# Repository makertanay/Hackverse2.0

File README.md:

# Rakshak

 application which will be a GPS tracker connected to an ambulance. In many situations we have seen that the ambulance doesn't reach some places on time as the place might be difficult to find, so by creating an application through which the ambulance and the person called for ambulance gets and idea of where the ambulance is and not only that application tells you where the ambulance is but until it arrives it also tells you what first aid can you give it to the patient at the moment so as to keep the person alive until he reaches the hospital.

### Unique Selling Points

* Point 1. it has a GPS locator, so the person called in for an ambulance can track where the ambulance is.
* Point 2. It tells you some First Aid that can be provided to the patients
* Point 3. This can work even in remote areas as it is inked with the google maps
* Point 4. This also shows how much time will it take to reach the patient

## Implementation: 
Enter the details, the details would be given to the nearest ambulance then the website will show the fastest direction for the ambulance to reach the victim in the mean time it will show the first aid that can be given to the patient.
## Technology Stack  

### Tech1

fusion360

### Tech2

aruduino 

### Tech3

WebDev

## Picture/Screenshot 1

## Picture/Screenshot 2

## Picture/Screenshot 3

## Challanges
Implementation was difficult due to constraint on hardware usage.

## Getting Started

https://makertanay.github.io/Hackverse2.0/

## Future Aspects

Implementation with Hardware

## Authors
* [**Tanay**]https://github.com/makertanay
* [**Kaustubh**]https://github.com/kaustubhmohta
* [**Gauri**]https://github.com/kodekandy

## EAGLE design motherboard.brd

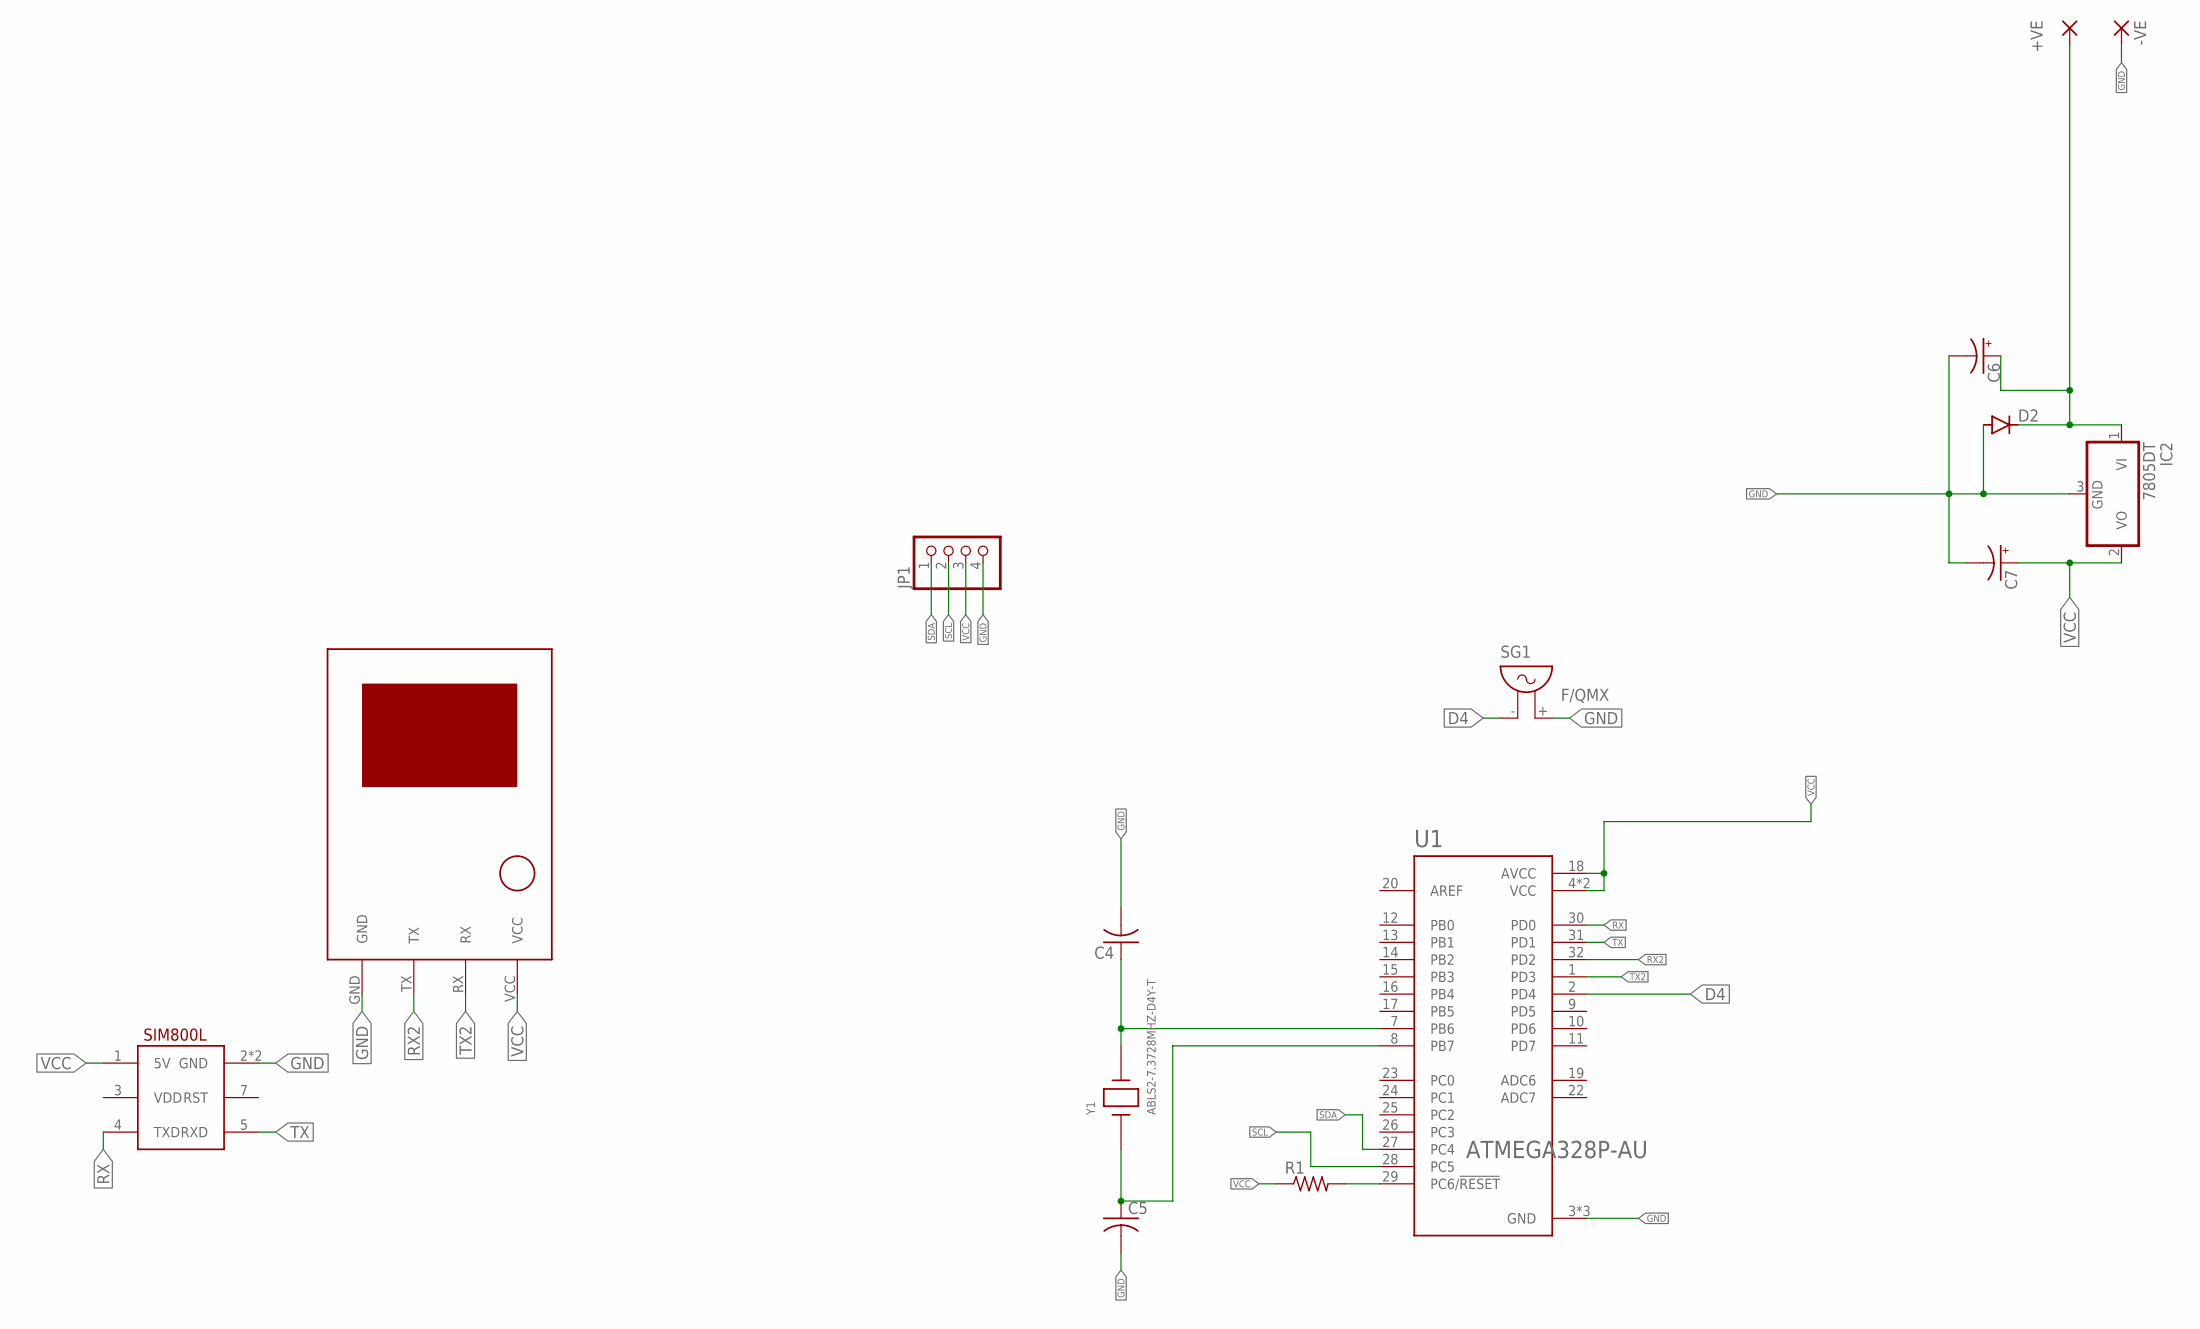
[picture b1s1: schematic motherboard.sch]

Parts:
+VE: WIREPAD1,6/0,8; 1,6/0,8
-VE: WIREPAD1,6/0,8; 1,6/0,8
C4, C5: C-US025-024X044; C025-024X044
C6, C7: CPOL-US153CLV-1010; 153CLV-1010
D2: DIODE-DO214AC; DO214AC
IC2: 7805DT; TO252
JP1: PINHD-1X4; 1X04
R1: R-US_R0603; R0603
SG1: F/QMX
U1: ATMEGA328P-AU; QFP80P900X900X120-32N
U$1: U-BLOX-NEO6V2
U$2: SIM800L; SIP
Y1: ABLS2-7.3728MHZ-D4Y-T; XTAL_ABLS2-7.3728MHZ-D4Y-T

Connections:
D4: SG1.- (1), U1.2 (PD4)
GND: -VE.1, C4.2, C5.2, C6.-, C7.-, D2.A, IC2.3 (GND), JP1.4, SG1.+ (2), U1.3 (GND), U1.5 (GND), U1.21 (GND), U$1.GND, U$2.2 (GND), U$2.6 (GND)
unnamed: +VE.1, C6.+, D2.C, IC2.1 (VI)
unnamed: C4.1, U1.7 (PB6), Y1.2
unnamed: C5.1, U1.8 (PB7), Y1.1
unnamed: R1.2, U1.29 (PC6/!RESET)
RX: U1.30 (PD0), U$2.4 (TXD)
RX2: U1.32 (PD2), U$1.TX
SCL: JP1.2, U1.28 (PC5)
SDA: JP1.1, U1.27 (PC4)
TX: U1.31 (PD1), U$2.5 (RXD)
TX2: U1.1 (PD3), U$1.RX
VCC: C7.+, IC2.2 (VO), JP1.3, R1.1, U1.4 (VCC), U1.6 (VCC), U1.18 (AVCC), U$1.VCC, U$2.1 (5V)

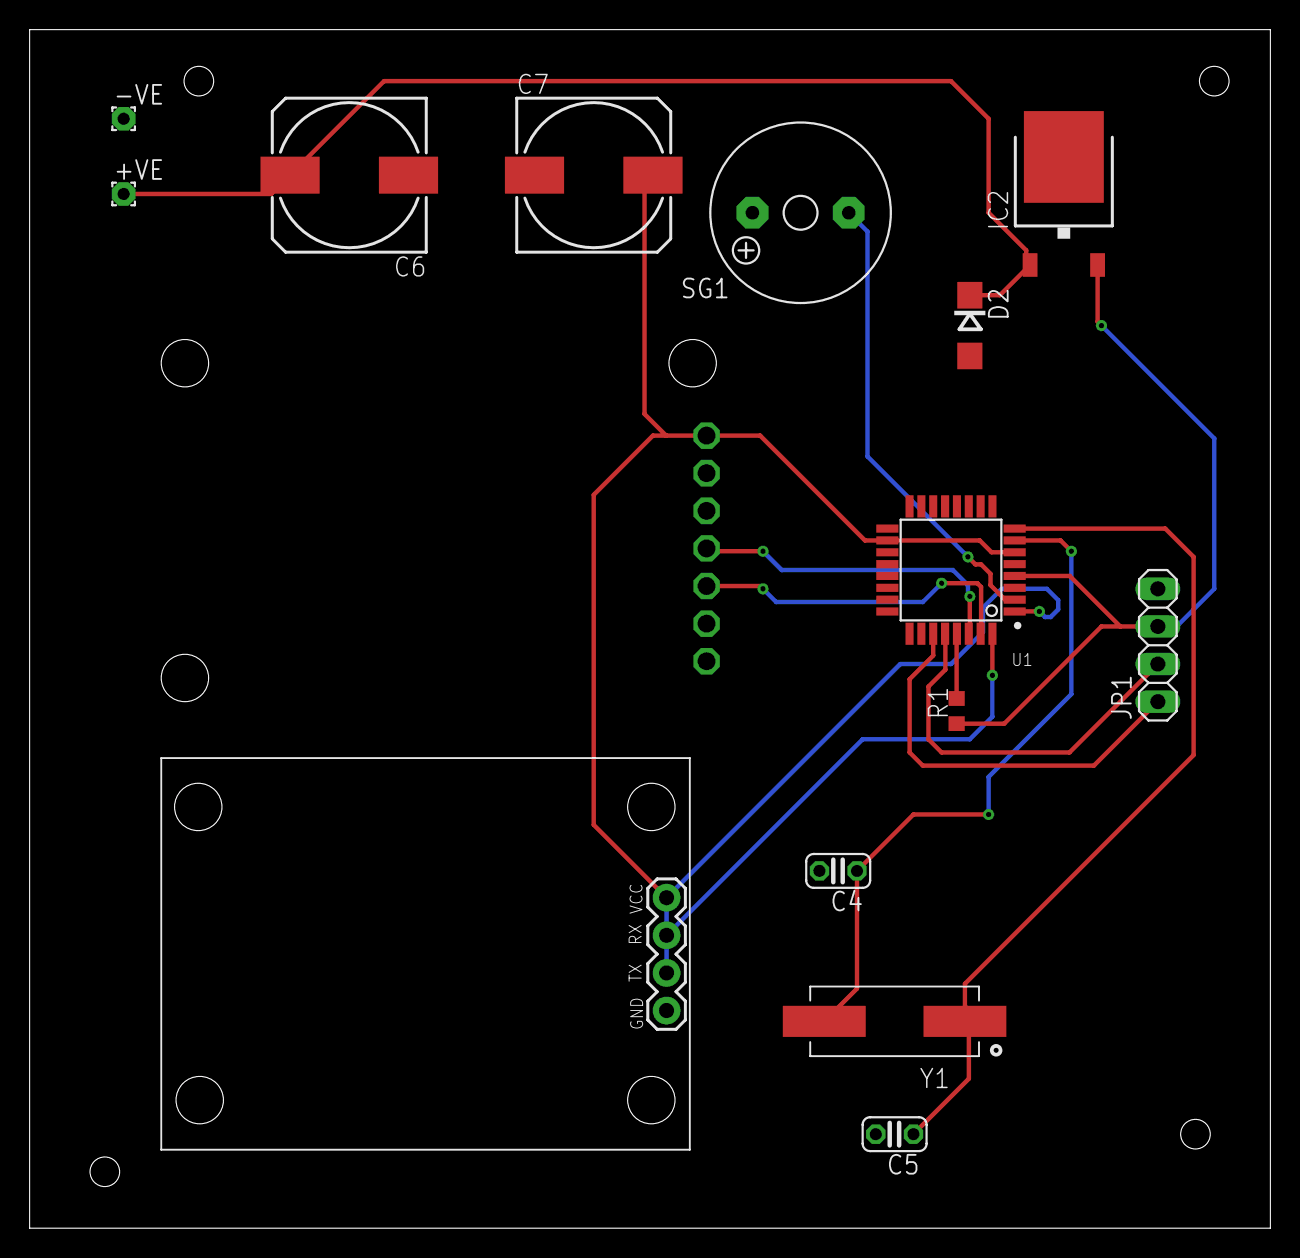
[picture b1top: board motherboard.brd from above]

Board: 2 copper layers, 83.8 x 81.0 mm, 15 parts (0 on the bottom side), 13 nets.

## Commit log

2021-02-28 Add files via upload
    PCB design for the Project
2021-02-28 Webite :tada:
2021-02-28 README update :sparkles:
